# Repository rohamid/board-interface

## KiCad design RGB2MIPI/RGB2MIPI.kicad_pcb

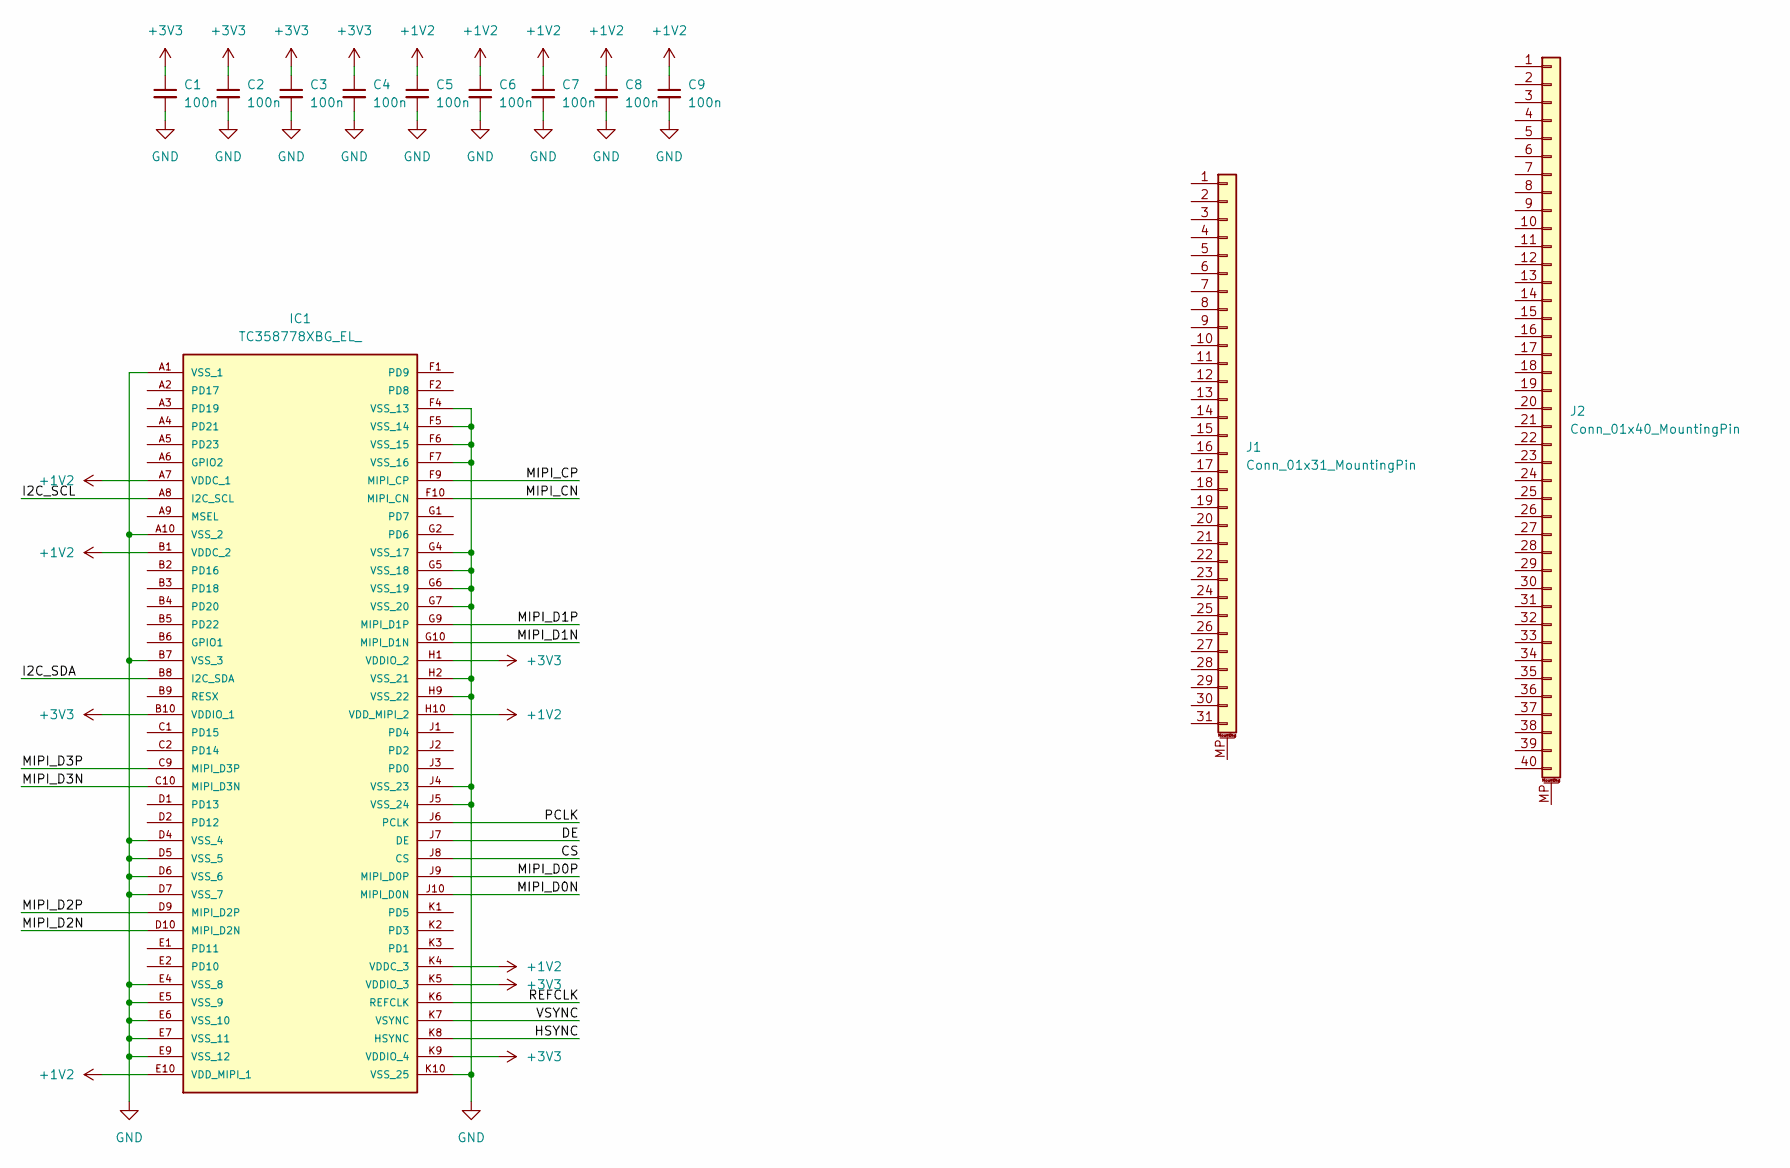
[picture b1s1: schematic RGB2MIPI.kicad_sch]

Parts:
C1, C2, C3, C4, C5, C6, C7, C8, C9: 100n; C_0201_0603Metric
IC1: TC358778XBG_EL_; BGA80C65P10X10_700X700X100; MOUSER_PART_NUMBER 757-TC358778XBGEL
J1: Conn_01x31_MountingPin; TE_3-1734839-1_1x31-1MP_P0.5mm_Horizontal
J2: Conn_01x40_MountingPin; Omron_XF2M-4015-1A_1x40-1MP_P0.5mm_Horizontal

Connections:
+1V2: C5.1, C6.1, C7.1, C8.1, C9.1, IC1.A7 (VDDC_1), IC1.B1 (VDDC_2), IC1.E10 (VDD_MIPI_1), IC1.H10 (VDD_MIPI_2), IC1.K4 (VDDC_3)
+3V3: C1.1, C2.1, C3.1, C4.1, IC1.B10 (VDDIO_1), IC1.H1 (VDDIO_2), IC1.K5 (VDDIO_3), IC1.K9 (VDDIO_4)
/CS: IC1.J8 (CS)
/DE: IC1.J7 (DE)
/HSYNC: IC1.K8 (HSYNC)
/I2C_SCL: IC1.A8 (I2C_SCL)
/I2C_SDA: IC1.B8 (I2C_SDA)
/MIPI_CN: IC1.F10 (MIPI_CN)
/MIPI_CP: IC1.F9 (MIPI_CP)
/MIPI_D0N: IC1.J10 (MIPI_D0N)
/MIPI_D0P: IC1.J9 (MIPI_D0P)
/MIPI_D1N: IC1.G10 (MIPI_D1N)
/MIPI_D1P: IC1.G9 (MIPI_D1P)
/MIPI_D2N: IC1.D10 (MIPI_D2N)
/MIPI_D2P: IC1.D9 (MIPI_D2P)
/MIPI_D3N: IC1.C10 (MIPI_D3N)
/MIPI_D3P: IC1.C9 (MIPI_D3P)
/PCLK: IC1.J6 (PCLK)
/REFCLK: IC1.K6 (REFCLK)
/VSYNC: IC1.K7 (VSYNC)
GND: C1.2, C2.2, C3.2, C4.2, C5.2, C6.2, C7.2, C8.2, C9.2, IC1.A1 (VSS_1), IC1.A10 (VSS_2), IC1.B7 (VSS_3), IC1.D4 (VSS_4), IC1.D5 (VSS_5), IC1.D6 (VSS_6), IC1.D7 (VSS_7), IC1.E4 (VSS_8), IC1.E5 (VSS_9), IC1.E6 (VSS_10), IC1.E7 (VSS_11), IC1.E9 (VSS_12), IC1.F4 (VSS_13), IC1.F5 (VSS_14), IC1.F6 (VSS_15), IC1.F7 (VSS_16), IC1.G4 (VSS_17), IC1.G5 (VSS_18), IC1.G6 (VSS_19), IC1.G7 (VSS_20), IC1.H2 (VSS_21), IC1.H9 (VSS_22), IC1.J4 (VSS_23), IC1.J5 (VSS_24), IC1.K10 (VSS_25)

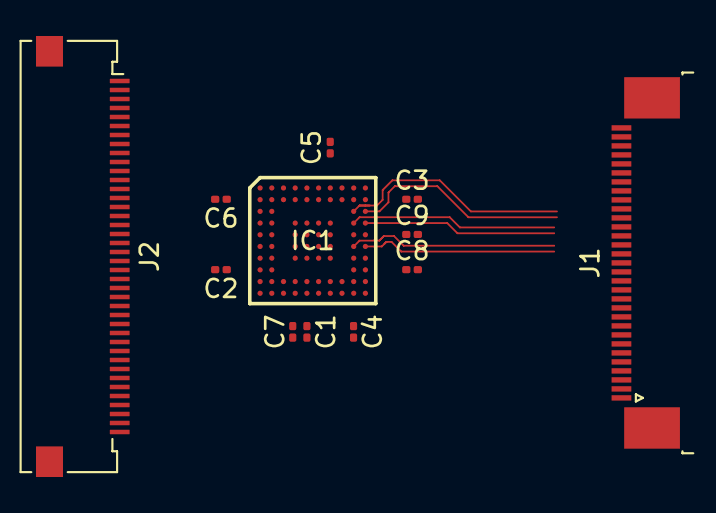
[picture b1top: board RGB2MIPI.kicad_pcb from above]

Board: 2 copper layers, 12 parts (0 on the bottom side), 3 nets.
